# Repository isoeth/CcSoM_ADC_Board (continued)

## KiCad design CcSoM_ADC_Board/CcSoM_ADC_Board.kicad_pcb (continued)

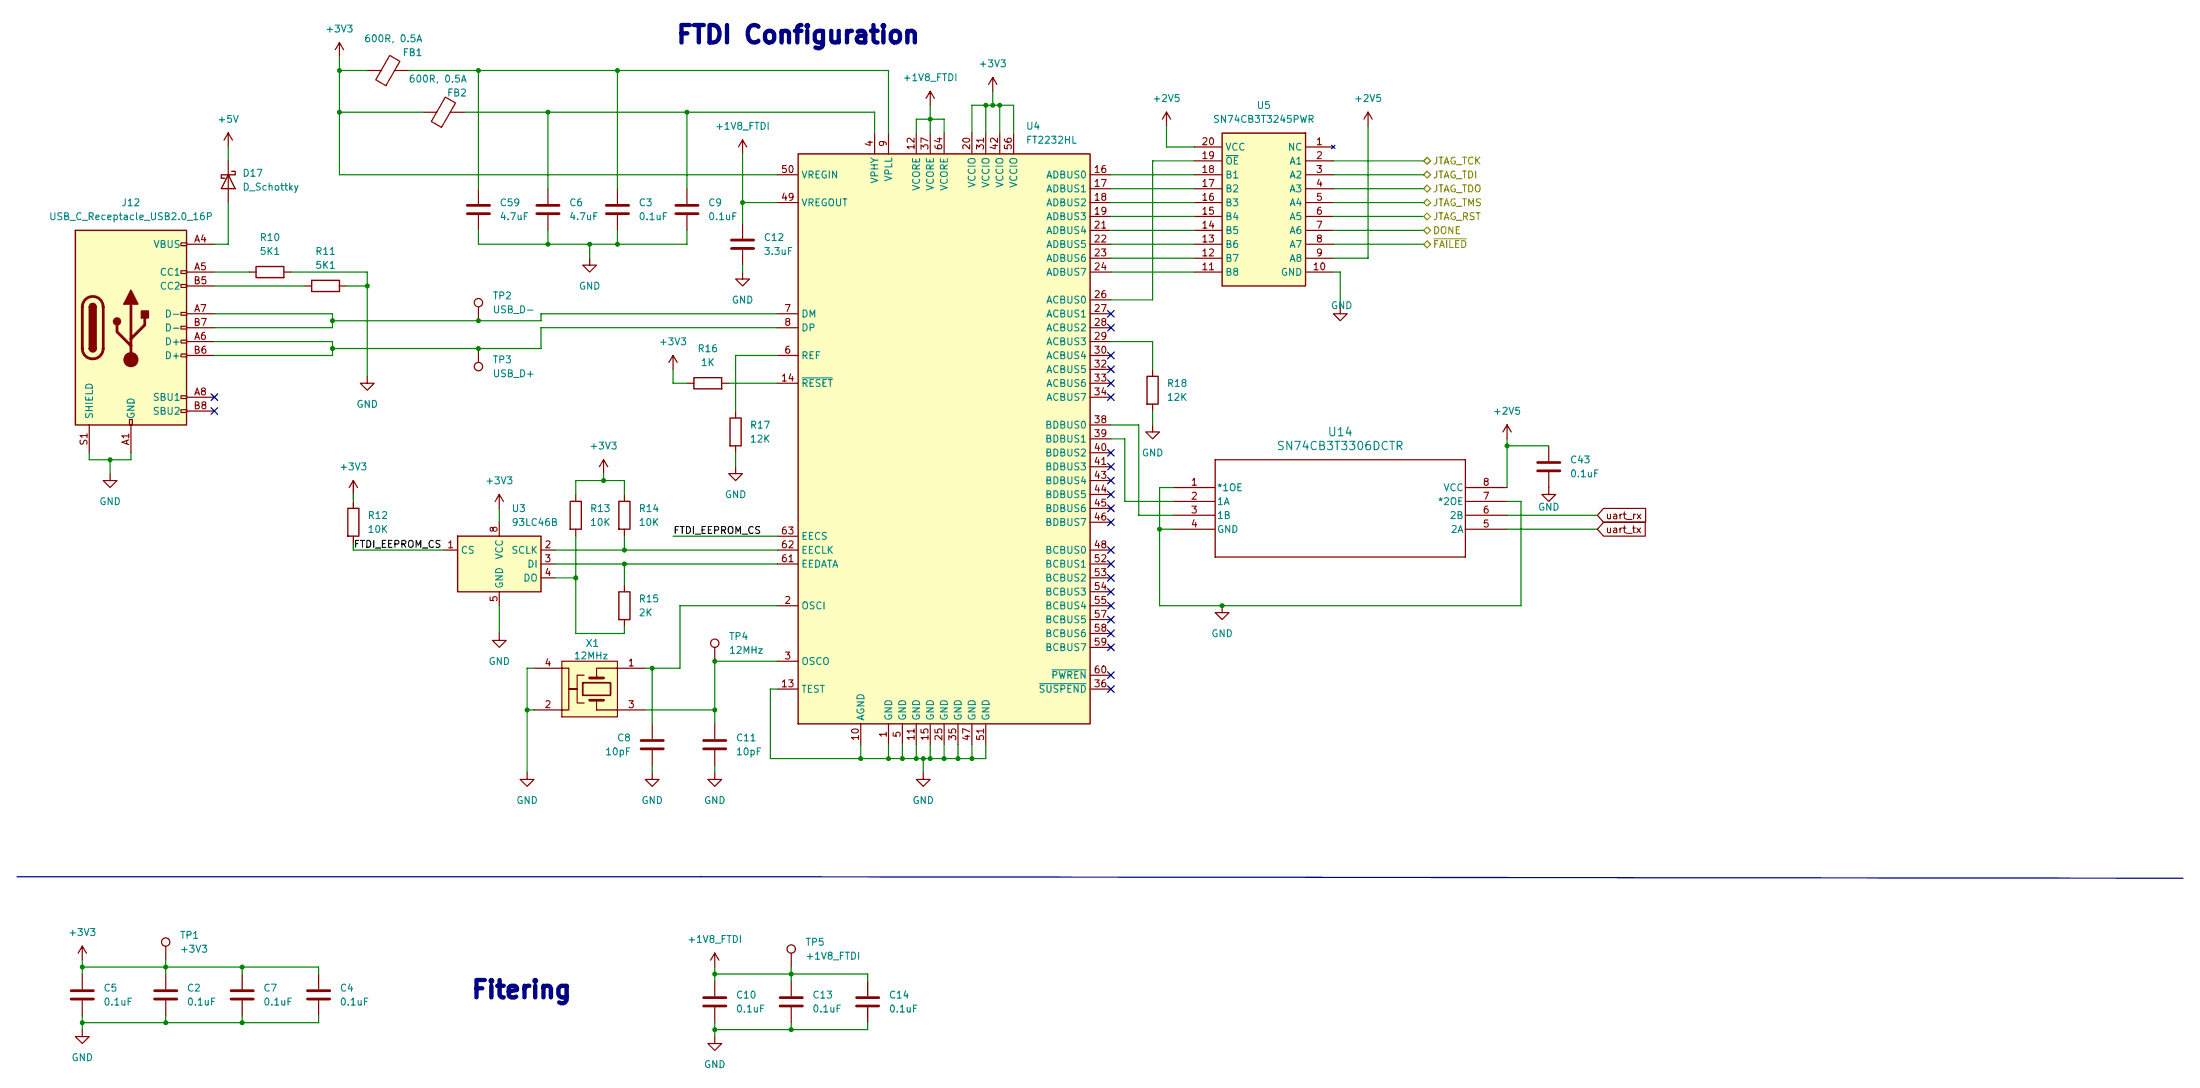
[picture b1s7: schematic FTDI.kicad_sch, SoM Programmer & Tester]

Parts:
C2, C3, C4, C5, C7, C9, C10, C13, C14, C43: 0.1uF; C_0603_1608Metric; Mouser Part Number 80-C0603C104M4R7411
C6, C59: 4.7uF; C_0603_1608Metric; Mouser Part Number 963-MSASE168AB5475KT
C8, C11: 10pF; C_0603_1608Metric; Mouser Part Number 581-0603YA100JAT2A
C12: 3.3uF; C_0603_1608Metric; Mouser Part Number 810-C1608X5R1C335KAC
D17: D_Schottky; D_0805_2012Metric_Pad1.15x1.40mm_HandSolder; DigiKey_no 478-7800-1-ND
FB1, FB2: 600R, 0.5A; L_0603_1608Metric; Mouser Part Number 810-MMZ1608R601ATD25
J12: USB_C_Receptacle_USB2.0_16P; USB_C_Receptacle_GCT_USB4110; Mouser Part Number 640-USB4110-GF-A
R10, R11: 5K1; R_0603_1608Metric; Mouser Part Number 71-RCS060356K0FKEA
R12, R13, R14: 10K; R_0603_1608Metric; Mouser Part Number 71-CRCW060310K0FKED
R15: 2K; R_0603_1608Metric; Mouser Part Number 71-TNPW06032K00FHEA
R16: 1K; R_0603_1608Metric; Mouser Part Number 71-CRCW0603-1.0K-E3
R17, R18: 12K; R_0603_1608Metric; Mouser Part Number 71-CRCW0603-12K-E3
TP1: +3V3; TestPoint_Pad_D1.5mm
TP2: USB_D-; TestPoint_Pad_D1.5mm
TP3: USB_D+; TestPoint_Pad_D1.5mm
TP4: 12MHz; TestPoint_Pad_D1.5mm
TP5: +1V8_FTDI; TestPoint_Pad_D1.5mm
U3: 93LC46B; TSSOP-8_4.4x3mm_P0.65mm; Mouser Part Number 579-93LC46BT-E/ST
U4: FT2232HL; LQFP-64_10x10mm_P0.5mm; Mouser Part Number 895-FT2232HL
U5: SN74CB3T3245PWR; TSSOP-20_4.4x6.5mm_P0.65mm; Mouser Part Number 595-SN74CB3T3245PWR
U14: SN74CB3T3306DCTR; DCT8; DigiKey_no 296-15553-1-ND
X1: 12MHz; Crystal_SMD_Abracon_ABM3B-4Pin_5.0x3.2mm; Mouser Part Number 815-ABM3B-12-T

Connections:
+1V8_FTDI: C10.1, C12.1, C13.1, C14.1, TP5.1 (1_1), U4.12 (VCORE), U4.37 (VCORE), U4.49 (VREGOUT), U4.64 (VCORE)
+3V3: C2.1, C4.1, C5.1, C7.1, FB1.1, FB2.1, R12.1, R13.1, R14.1, R16.1, TP1.1 (1_1), U3.8 (VCC), U4.20 (VCCIO), U4.31 (VCCIO), U4.42 (VCCIO), U4.50 (VREGIN), U4.56 (VCCIO); also elsewhere on the board
+5V: D17.1 (K); also elsewhere on the board
/DONE: U5.7 (A6); also elsewhere on the board
/FTDI/FTDI_EEPROM_CS: R12.2, U3.1 (CS), U4.63 (EECS)
/FTDI/JTAG_RST: U5.6 (A5); also elsewhere on the board
/FTDI/JTAG_TCK: U5.2 (A1); also elsewhere on the board
/FTDI/JTAG_TDI: U5.3 (A2); also elsewhere on the board
/FTDI/JTAG_TDO: U5.4 (A3); also elsewhere on the board
/FTDI/JTAG_TMS: U5.5 (A4); also elsewhere on the board
/~FAILED: U5.8 (A7); also elsewhere on the board
unnamed: D17.2 (A), J12.A4 (VBUS), J12.A9 (VBUS), J12.B4 (VBUS), J12.B9 (VBUS)
unnamed: J12.A5 (CC1), R10.1
unnamed: J12.B5 (CC2), R11.2
unnamed: R15.1, U3.3 (DI), U4.61 (EEDATA)
unnamed: R13.2, R15.2, U3.4 (DO)
unnamed: R14.2, U3.2 (SCLK), U4.62 (EECLK)
unnamed: U4.26 (ACBUS0), U5.19 (~OE)
unnamed: R18.1, U4.29 (ACBUS3)
unnamed: U4.16 (ADBUS0), U5.18 (B1)
unnamed: U4.17 (ADBUS1), U5.17 (B2)
unnamed: U4.18 (ADBUS2), U5.16 (B3)
unnamed: U4.19 (ADBUS3), U5.15 (B4)
unnamed: U4.21 (ADBUS4), U5.14 (B5)
unnamed: U4.22 (ADBUS5), U5.13 (B6)
unnamed: U4.23 (ADBUS6), U5.12 (B7)
unnamed: U4.24 (ADBUS7), U5.11 (B8)
unnamed: J12.A7 (D-), J12.B7 (D-), TP2.1 (1_1), U4.7 (DM)
unnamed: J12.A6 (D+), J12.B6 (D+), TP3.1 (1_1), U4.8 (DP)
unnamed: C8.1, U4.2 (OSCI), X1.1
unnamed: C11.1, TP4.1 (1_1), U4.3 (OSCO), X1.3
unnamed: R17.1, U4.6 (REF)
unnamed: C6.1, C9.1, FB2.2, U4.4 (VPHY)
unnamed: C3.1, C59.1, FB1.2, U4.9 (VPLL)
unnamed: R16.2, U4.14 (~RESET)
unnamed: U4.39 (BDBUS1), U14.2 (1A)
unnamed: U4.38 (BDBUS0), U14.3 (1B)
OGND: C2.2, C3.2, C4.2, C5.2, C6.2, C7.2, C8.2, C9.2, C10.2, C11.2, C12.2, C13.2, C14.2, C43.1, C59.2, J12.A1 (GND), J12.A12 (GND), J12.B1 (GND), J12.B12 (GND), J12.S1 (SHIELD), R10.2, R11.1, R17.2, R18.2, U3.5 (GND), U4.1 (GND), U4.5 (GND), U4.10 (AGND), U4.11 (GND), U4.13 (TEST), U4.15 (GND), U4.25 (GND), U4.35 (GND), U4.47 (GND), U4.51 (GND), U5.10 (GND), U14.1 (*1OE), U14.4 (GND), U14.7 (*2OE), X1.2, X1.4; also elsewhere on the board
OVDD: C43.2, U5.9 (A8), U5.20 (VCC), U14.8 (VCC); also elsewhere on the board
uart_rx: U14.6 (2B); also elsewhere on the board
uart_tx: U14.5 (2A); also elsewhere on the board

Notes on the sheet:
Fitering
FTDI Configuration

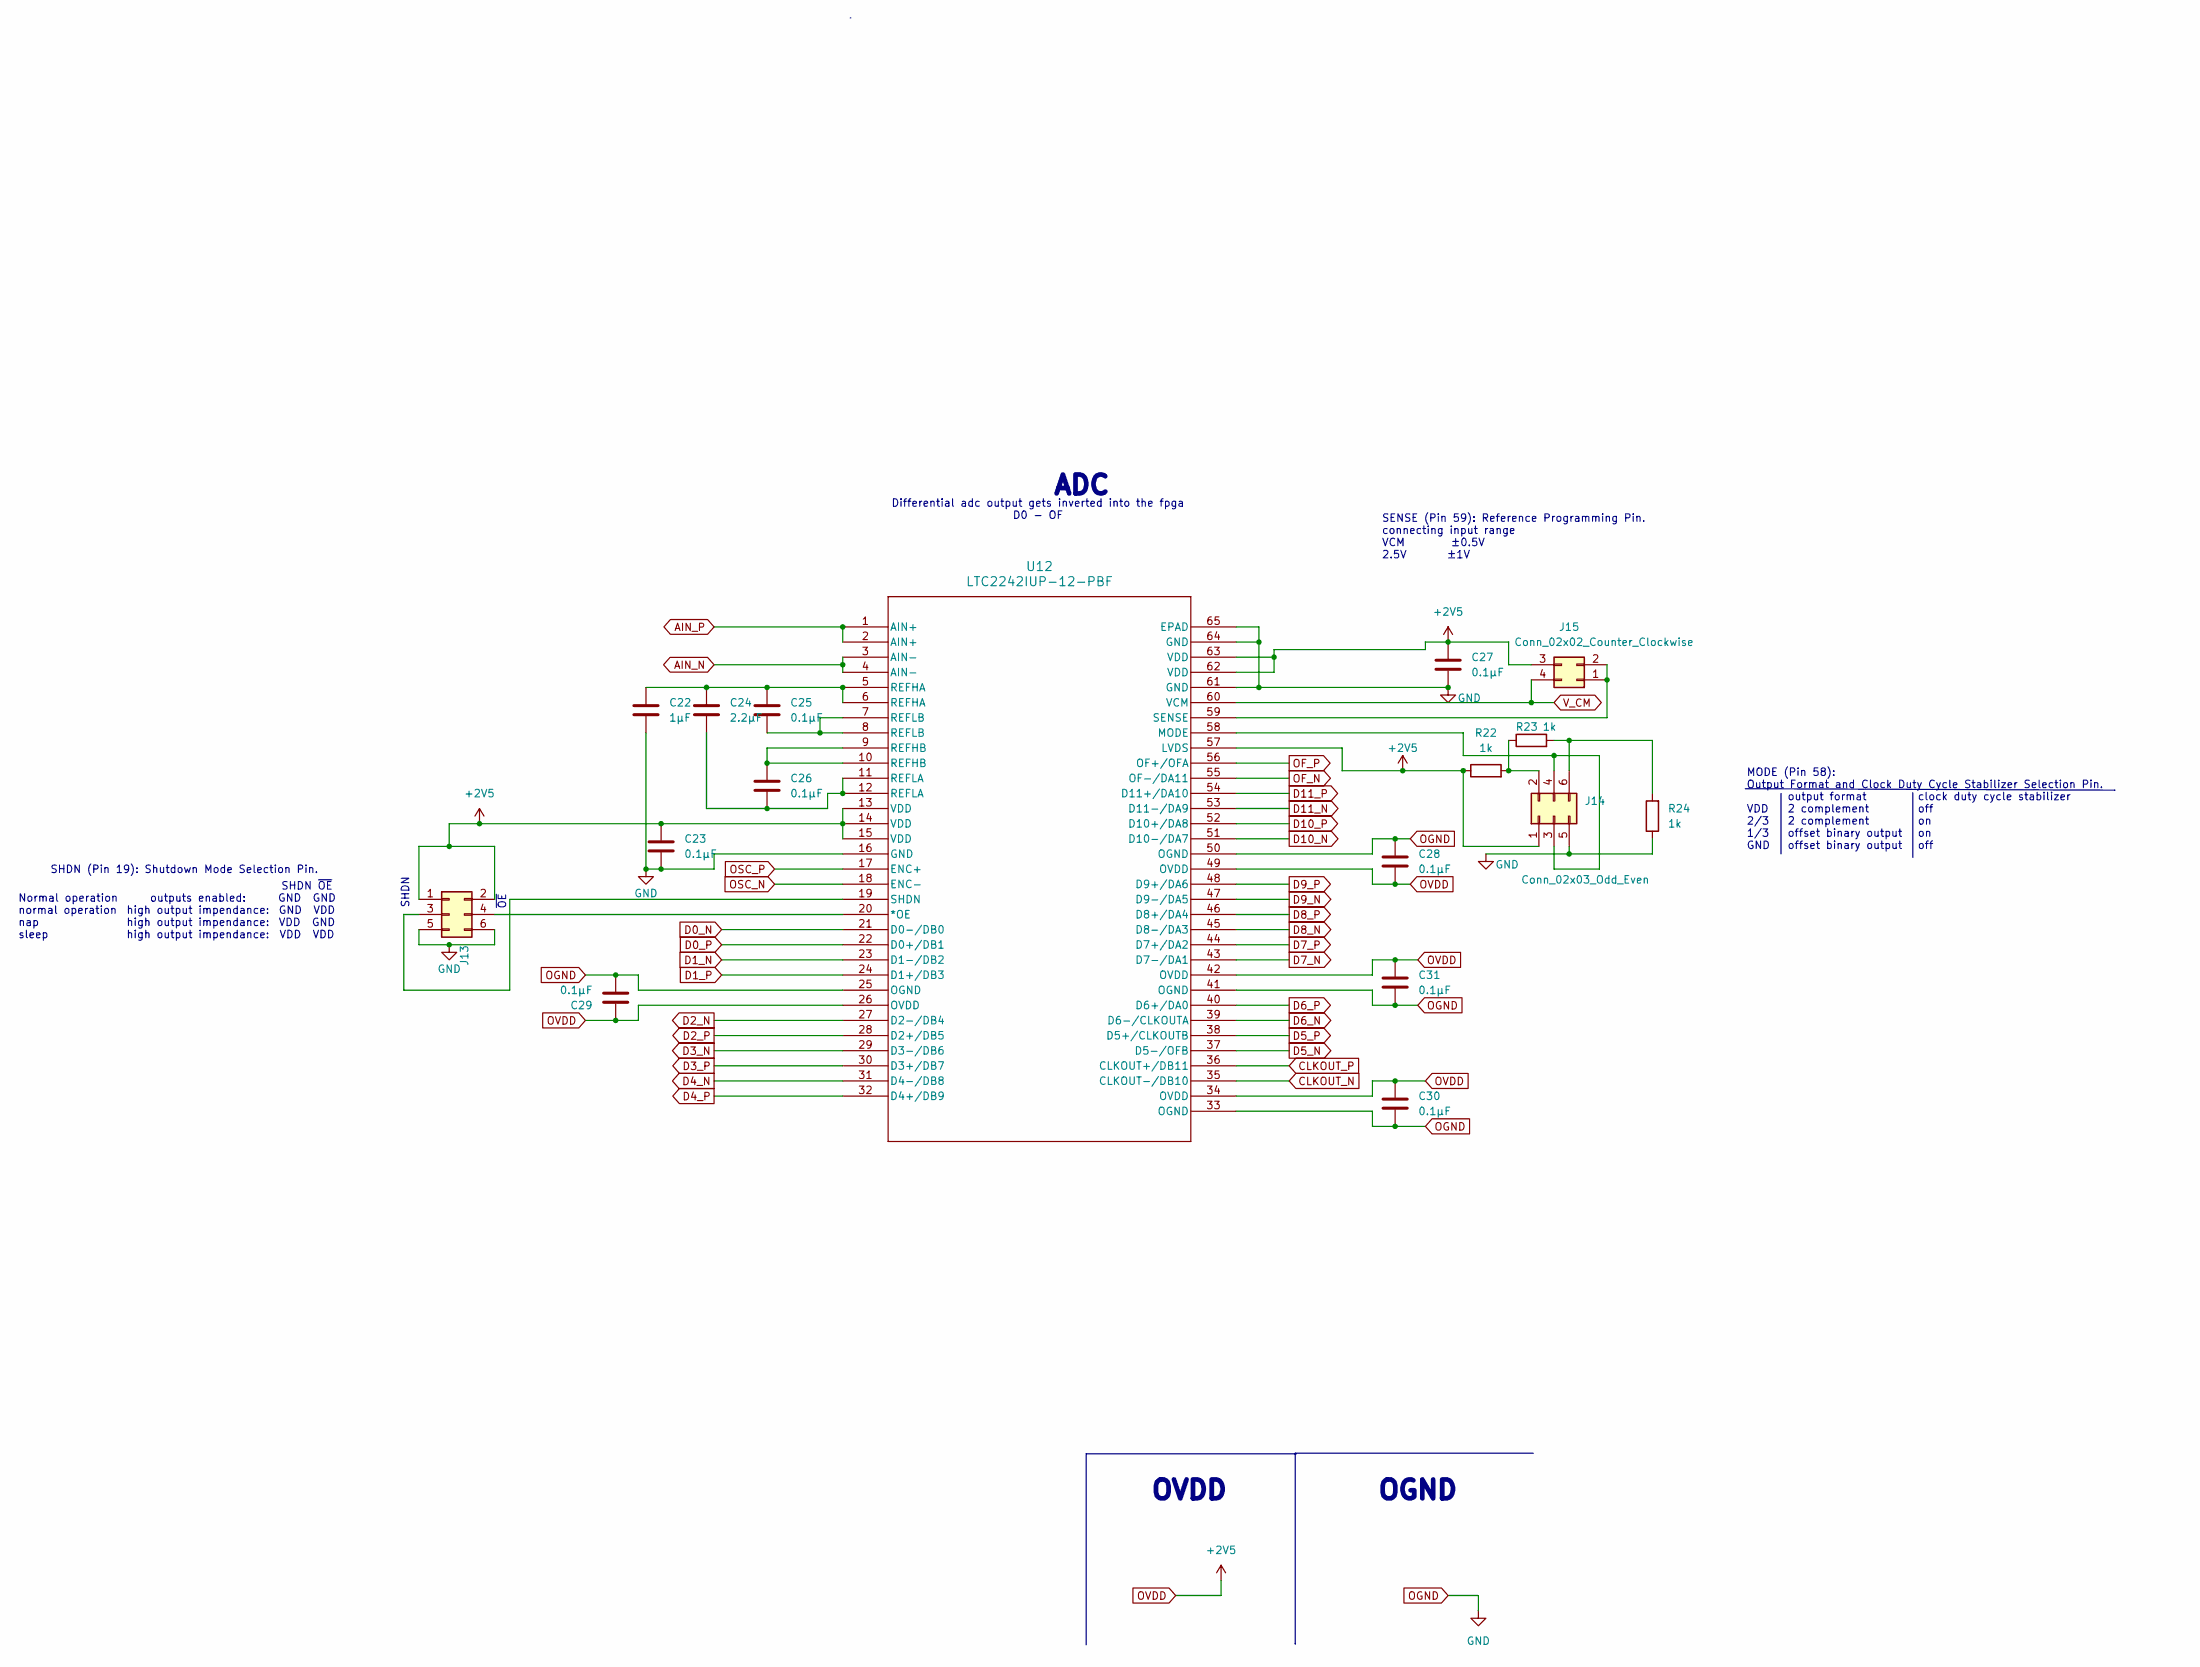
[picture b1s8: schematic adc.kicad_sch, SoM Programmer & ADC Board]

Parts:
C22: 1μF; C_0603_1608Metric; DigiKey_no 399-C0603C105K4RACTUCT-ND
C23, C25, C26, C27, C28, C29, C30, C31: 0.1μF; C_0603_1608Metric; DigiKey_no 399-C0603X103J4HACAUTOCT-ND
C24: 2.2μF; C_0603_1608Metric; DigiKey_no 1276-1040-1-ND
J13, J14: Conn_02x03_Odd_Even; PinHeader_2x03_P2.54mm_Vertical; DigiKey_no 609-3234-ND
J15: Conn_02x02_Counter_Clockwise; PinHeader_2x02_P2.54mm_Vertical; DigiKey_no 609-3233-ND
R22, R23, R24: 1k; R_0603_1608Metric; DigiKey_no 541-1.00KHCT-ND
U12: LTC2242IUP-12-PBF; QFN-64_UP_LIT; DigiKey_no LTC2242IUP-12#PBF-ND

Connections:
AIN_N: U12.3 (AIN-), U12.4 (AIN-); also elsewhere on the board
AIN_P: U12.1 (AIN+), U12.2 (AIN+); also elsewhere on the board
CLKOUT_N: U12.35 (CLKOUT-/DB10); also elsewhere on the board
CLKOUT_P: U12.36 (CLKOUT+/DB11); also elsewhere on the board
D0_N: U12.21 (D0-/DB0); also elsewhere on the board
D0_P: U12.22 (D0+/DB1); also elsewhere on the board
D1_N: U12.23 (D1-/DB2); also elsewhere on the board
D1_P: U12.24 (D1+/DB3); also elsewhere on the board
D2_N: U12.27 (D2-/DB4); also elsewhere on the board
D2_P: U12.28 (D2+/DB5); also elsewhere on the board
D3_N: U12.29 (D3-/DB6); also elsewhere on the board
D3_P: U12.30 (D3+/DB7); also elsewhere on the board
D4_N: U12.31 (D4-/DB8); also elsewhere on the board
D4_P: U12.32 (D4+/DB9); also elsewhere on the board
D5_N: U12.37 (D5-/OFB); also elsewhere on the board
D5_P: U12.38 (D5+/CLKOUTB); also elsewhere on the board
D6_N: U12.39 (D6-/CLKOUTA); also elsewhere on the board
D6_P: U12.40 (D6+/DA0); also elsewhere on the board
D7_N: U12.43 (D7-/DA1); also elsewhere on the board
D7_P: U12.44 (D7+/DA2); also elsewhere on the board
D8_N: U12.45 (D8-/DA3); also elsewhere on the board
D8_P: U12.46 (D8+/DA4); also elsewhere on the board
D9_N: U12.47 (D9-/DA5); also elsewhere on the board
D9_P: U12.48 (D9+/DA6); also elsewhere on the board
D10_N: U12.51 (D10-/DA7); also elsewhere on the board
D10_P: U12.52 (D10+/DA8); also elsewhere on the board
D11_N: U12.53 (D11-/DA9); also elsewhere on the board
D11_P: U12.54 (D11+/DA10); also elsewhere on the board
unnamed: C22.1, C24.1, C25.1, U12.5 (REFHA), U12.6 (REFHA)
unnamed: C24.2, C26.2, U12.11 (REFLA), U12.12 (REFLA)
unnamed: C25.2, U12.7 (REFLB), U12.8 (REFLB)
unnamed: C26.1, U12.9 (REFHB), U12.10 (REFHB)
unnamed: J13.3, U12.19 (SHDN)
unnamed: J13.4, U12.20 (*OE)
unnamed: J14.2, R22.2, R23.1
unnamed: J14.3, J14.4, U12.58 (MODE)
unnamed: J14.6, R23.2, R24.2
unnamed: J15.1, J15.2, U12.59 (SENSE)
OF_N: U12.55 (OF-/DA11); also elsewhere on the board
OF_P: U12.56 (OF+/OFA); also elsewhere on the board
OGND: C22.2, C23.2, C27.1, C28.1, C29.1, C30.2, C31.2, J13.5, J13.6, J14.5, R24.1, U12.16 (GND), U12.25 (OGND), U12.33 (OGND), U12.41 (OGND), U12.50 (OGND), U12.61 (GND), U12.64 (GND), U12.65 (EPAD); also elsewhere on the board
OSC_N: U12.18 (ENC-); also elsewhere on the board
OSC_P: U12.17 (ENC+); also elsewhere on the board
OVDD: C23.1, C27.2, C28.2, C29.2, C30.1, C31.1, J13.1, J13.2, J14.1, J15.3, R22.1, U12.13 (VDD), U12.14 (VDD), U12.15 (VDD), U12.26 (OVDD), U12.34 (OVDD), U12.42 (OVDD), U12.49 (OVDD), U12.57 (LVDS), U12.62 (VDD), U12.63 (VDD); also elsewhere on the board
V_CM: J15.4, U12.60 (VCM); also elsewhere on the board

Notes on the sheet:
SENSE (Pin 59): Reference Programming Pin. connecting input range VCM ±0.5V 2.5V ±1V
Normal operation normal operation nap sleep
OGND
SHDN
OVDD
SHDN ~{OE} GND GND GND VDD VDD GND VDD VDD
SHDN (Pin 19): Shutdown Mode Selection Pin.
Differential adc output gets inverted into the fpga D0 - OF
ADC
MODE (Pin 58): Output Format and Clock Duty Cycle Stabilizer Selection Pin. VDD 2/3 1/3 GND
outputs enabled: high output impendance: high output impendance: high output impendance:
output format 2 complement 2 complement offset binary output offset binary output
~{OE}
clock duty cycle stabilizer off on on off

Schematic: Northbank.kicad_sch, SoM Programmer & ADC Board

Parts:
J1: SoM Connector; SoM_Connector; Mouser Part Number 571-1-1473005-1

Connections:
/Header Interface/Northbank/VDD_NA: J1.9 (VDD_NA); also elsewhere on the board
/Header Interface/Northbank/VDD_NB: J1.5 (VDD_NB); also elsewhere on the board
G_CLK25: J1.192 (NA4_P); also elsewhere on the board
G_CLK125: J1.190 (NA4_N); also elsewhere on the board
G_MAC_MDIO: J1.188 (NA6_N); also elsewhere on the board
G_PHY_RST: J1.184 (NA8_N); also elsewhere on the board
G_PHY_RXCTL: J1.168 (NB5_P); also elsewhere on the board
G_PHY_RXD2: J1.164 (NB8_N); also elsewhere on the board
G_PHY_RXD3: J1.166 (NB8_P); also elsewhere on the board
G_PHY_TXCTL: J1.170 (NB5_N); also elsewhere on the board
G_PHY_TXD0: J1.172 (NB3_N); also elsewhere on the board
G_PHY_TXD1: J1.174 (NB3_P); also elsewhere on the board
G_PHY_TXD2: J1.176 (NB1_N); also elsewhere on the board
G_PHY_TXD3: J1.178 (NB1_P); also elsewhere on the board
G_PHY_TXEN: J1.182 (NA8_P); also elsewhere on the board
G_PS_MI052: J1.186 (NA6_P); also elsewhere on the board
NA1_N: J1.197 (NA1_N); also elsewhere on the board
NA1_P: J1.195 (NA1_P); also elsewhere on the board
NA3_N: J1.193 (NA3_N); also elsewhere on the board
NA3_P: J1.191 (NA3_P); also elsewhere on the board
NA5_N: J1.189 (NA5_N); also elsewhere on the board
NA5_P: J1.187 (NA5_P); also elsewhere on the board
NA7_N: J1.185 (NA7_N); also elsewhere on the board
NA7_P: J1.183 (NA7_P); also elsewhere on the board
NB0_N: J1.177 (NB0_N); also elsewhere on the board
NB0_P: J1.179 (NB0_P); also elsewhere on the board
NB2_N: J1.173 (NB2_N); also elsewhere on the board
NB2_P: J1.175 (NB2_P); also elsewhere on the board
NB4_N: J1.169 (NB4_N); also elsewhere on the board
NB4_P: J1.171 (NB4_P); also elsewhere on the board
NB6_N: J1.165 (NB6_N); also elsewhere on the board
NB6_P: J1.167 (NB6_P); also elsewhere on the board
NB7_N: J1.161 (NB7_N); also elsewhere on the board
NB7_P: J1.163 (NB7_P); also elsewhere on the board

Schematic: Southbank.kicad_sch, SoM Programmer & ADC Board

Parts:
J1: SoM Connector; SoM_Connector; Mouser Part Number 571-1-1473005-1

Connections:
/Header Interface/Southbank/VDD_SA: J1.16 (VDD_SA); also elsewhere on the board
D0_N: J1.109 (SB0_P); also elsewhere on the board
D0_P: J1.107 (SB0_N); also elsewhere on the board
D1_N: J1.95 (SA6_P); also elsewhere on the board
D1_P: J1.93 (SA6_N); also elsewhere on the board
D2_N: J1.91 (SA5_P); also elsewhere on the board
D2_P: J1.89 (SA5_N); also elsewhere on the board
D3_N: J1.87 (SA3_P); also elsewhere on the board
D3_P: J1.85 (SA3_N); also elsewhere on the board
D4_N: J1.83 (SA0_P); also elsewhere on the board
D4_P: J1.81 (SA0_N); also elsewhere on the board
OSC_N: J1.111 (SB1_N); also elsewhere on the board
OSC_P: J1.113 (SB1_P); also elsewhere on the board
SB2_N: J1.115 (SB2_N); also elsewhere on the board
SB2_P: J1.117 (SB2_P); also elsewhere on the board
SB3_N: J1.119 (SB3_N); also elsewhere on the board
SB3_P: J1.121 (SB3_P); also elsewhere on the board

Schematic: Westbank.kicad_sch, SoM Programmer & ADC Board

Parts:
J1: SoM Connector; SoM_Connector; Mouser Part Number 571-1-1473005-1

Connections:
/Header Interface/Westbank/VDD_WB: J1.12 (VDD_WB); also elsewhere on the board
/Header Interface/Westbank/VDD_WC: J1.8 (VDD_WC); also elsewhere on the board
CLKOUT_N: J1.79 (WB2_P); also elsewhere on the board
CLKOUT_P: J1.77 (WB2_N); also elsewhere on the board
D5_N: J1.75 (WB4_P); also elsewhere on the board
D5_P: J1.73 (WB4_N); also elsewhere on the board
D6_N: J1.71 (WB6_P); also elsewhere on the board
D6_P: J1.69 (WB6_N); also elsewhere on the board
D7_N: J1.67 (WB8_P); also elsewhere on the board
D7_P: J1.65 (WB8_N); also elsewhere on the board
D8_N: J1.63 (WC1_P); also elsewhere on the board
D8_P: J1.61 (WC1_N); also elsewhere on the board
D9_N: J1.59 (WC3_P); also elsewhere on the board
D9_P: J1.57 (WC3_N); also elsewhere on the board
D10_N: J1.55 (WC5_P); also elsewhere on the board
D10_P: J1.53 (WC5_N); also elsewhere on the board
D11_N: J1.51 (WC6_P); also elsewhere on the board
D11_P: J1.49 (WC6_N); also elsewhere on the board
NOT_ResetB: J1.58 (WC4_P); also elsewhere on the board
OF_N: J1.47 (WC7_P); also elsewhere on the board
OF_P: J1.45 (WC7_N); also elsewhere on the board
USB2_+: J1.86 (WB0_P); also elsewhere on the board
USB2_-: J1.84 (WB0_N); also elsewhere on the board
USB_DATA0: J1.66 (WC0_P); also elsewhere on the board
USB_DATA1: J1.68 (WB7_N); also elsewhere on the board
USB_DATA2: J1.70 (WB7_P); also elsewhere on the board
USB_DATA3: J1.72 (WB5_N); also elsewhere on the board
USB_DATA4: J1.74 (WB5_P); also elsewhere on the board
USB_DATA5: J1.76 (WB3_N); also elsewhere on the board
USB_DATA6: J1.78 (WB3_P); also elsewhere on the board
USB_DATA7: J1.80 (WB1_N); also elsewhere on the board
USB_DIR: J1.62 (WC2_P); also elsewhere on the board
USB_NXT: J1.64 (WC0_N); also elsewhere on the board
USB_REFCLK: J1.56 (WC4_N); also elsewhere on the board
USB_STP: J1.60 (WC2_N); also elsewhere on the board
uart_rx: J1.41 (WC8_N); also elsewhere on the board
uart_tx: J1.43 (WC8_P); also elsewhere on the board

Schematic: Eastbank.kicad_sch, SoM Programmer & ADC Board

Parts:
J1: SoM Connector; SoM_Connector; Mouser Part Number 571-1-1473005-1

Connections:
/Header Interface/Eastbank/VDD_EA: J1.13 (VDD_EA); also elsewhere on the board
/Header Interface/Eastbank/VDD_EB: J1.17 (VDD_EB); also elsewhere on the board
EA0_N: J1.123 (EA0_N); also elsewhere on the board
EA0_P: J1.125 (EA0_P); also elsewhere on the board
EA2_N: J1.129 (EA2_N); also elsewhere on the board
EA2_P: J1.127 (EA2_P); also elsewhere on the board
EA4_N: J1.133 (EA4_N); also elsewhere on the board
EA4_P: J1.131 (EA4_P); also elsewhere on the board
EA7_N: J1.137 (EA7_N); also elsewhere on the board
EA7_P: J1.135 (EA7_P); also elsewhere on the board
EB0_N: J1.141 (EB0_N); also elsewhere on the board
EB0_P: J1.139 (EB0_P); also elsewhere on the board
EB1_N: J1.148 (EB1_N); also elsewhere on the board
EB1_P: J1.146 (EB1_P); also elsewhere on the board
EB2_N: J1.145 (EB2_N); also elsewhere on the board
EB2_P: J1.143 (EB2_P); also elsewhere on the board
EB3_N: J1.152 (EB3_N); also elsewhere on the board
EB3_P: J1.150 (EB3_P); also elsewhere on the board
EB4_N: J1.149 (EB4_N)
EB4_P: J1.147 (EB4_P)
EB5_N: J1.153 (EB5_N); also elsewhere on the board
EB5_P: J1.151 (EB5_P); also elsewhere on the board
EB8_N: J1.155 (EB8_N); also elsewhere on the board
EB8_P: J1.157 (EB8_P); also elsewhere on the board
G_ETH_RXCTL: J1.156 (EB6_N); also elsewhere on the board
G_PHY_RXD0: J1.158 (EB7_N); also elsewhere on the board
G_PHY_RXD1: J1.160 (EB7_P); also elsewhere on the board

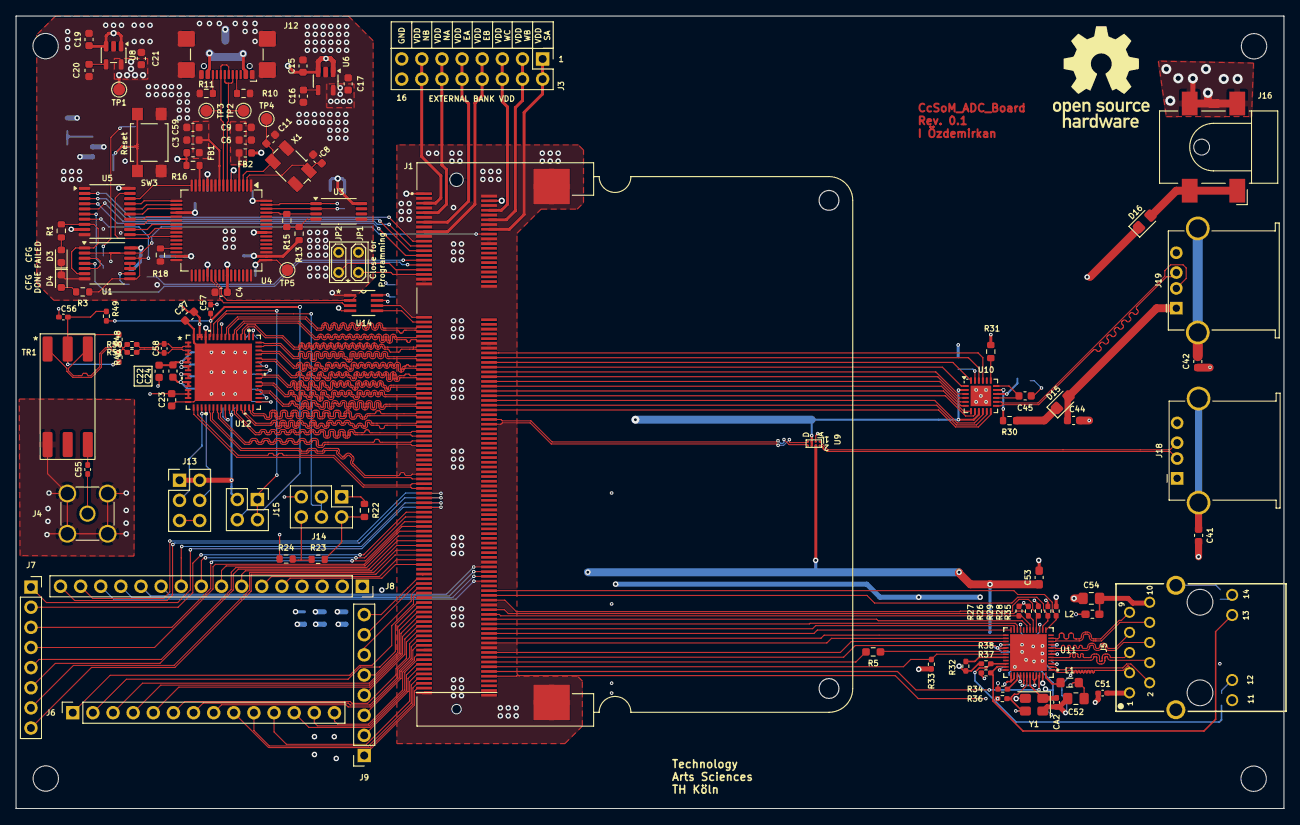
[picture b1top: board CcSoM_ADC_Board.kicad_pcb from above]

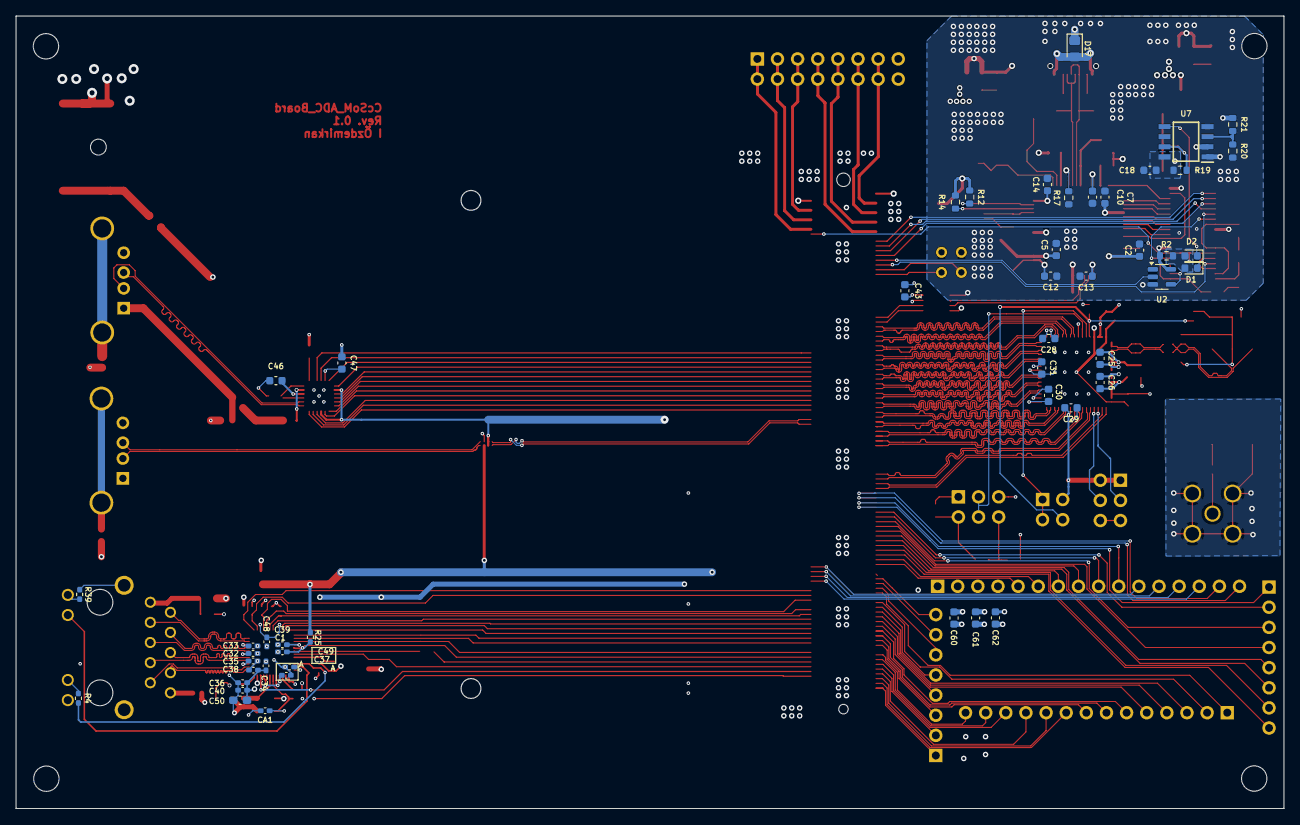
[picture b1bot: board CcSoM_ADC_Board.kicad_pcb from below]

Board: 4 copper layers, 160.0 x 100.0 mm, 159 parts (49 on the bottom side), 220 nets.

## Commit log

2026-01-28 init push
2026-01-28 deleted .swp file
2026-01-28 corrected link
2026-02-09 changed from 10Bit ADC to 12Bit
2026-02-09 corrected schematic created pdf and bom file
2026-02-09 changed some traces
2026-02-19 changed 10 bit to 12 bit
2026-02-25 moved designator and changed vddio to 2.5V
2026-03-04 last before rotating adc
2026-03-04 added kicad .gitignore
2026-03-04 changed schottky, began to add digikey part numbers
2026-03-11 digikey no not complete
2026-03-13 changed library path added symbols and footprints
2026-03-13 added datasheets deleted duplicate footprints
2026-03-16 changed footprint of pinheader from smd to through hole
2026-03-16 changed digikeyno from component, added info into readme about discontinued parts in digikey
2026-04-01 corrected differential pairs
2026-04-01 added pcb name on F.Mask
2026-04-17 changed traces
2026-04-17 added gerber files and other changes
